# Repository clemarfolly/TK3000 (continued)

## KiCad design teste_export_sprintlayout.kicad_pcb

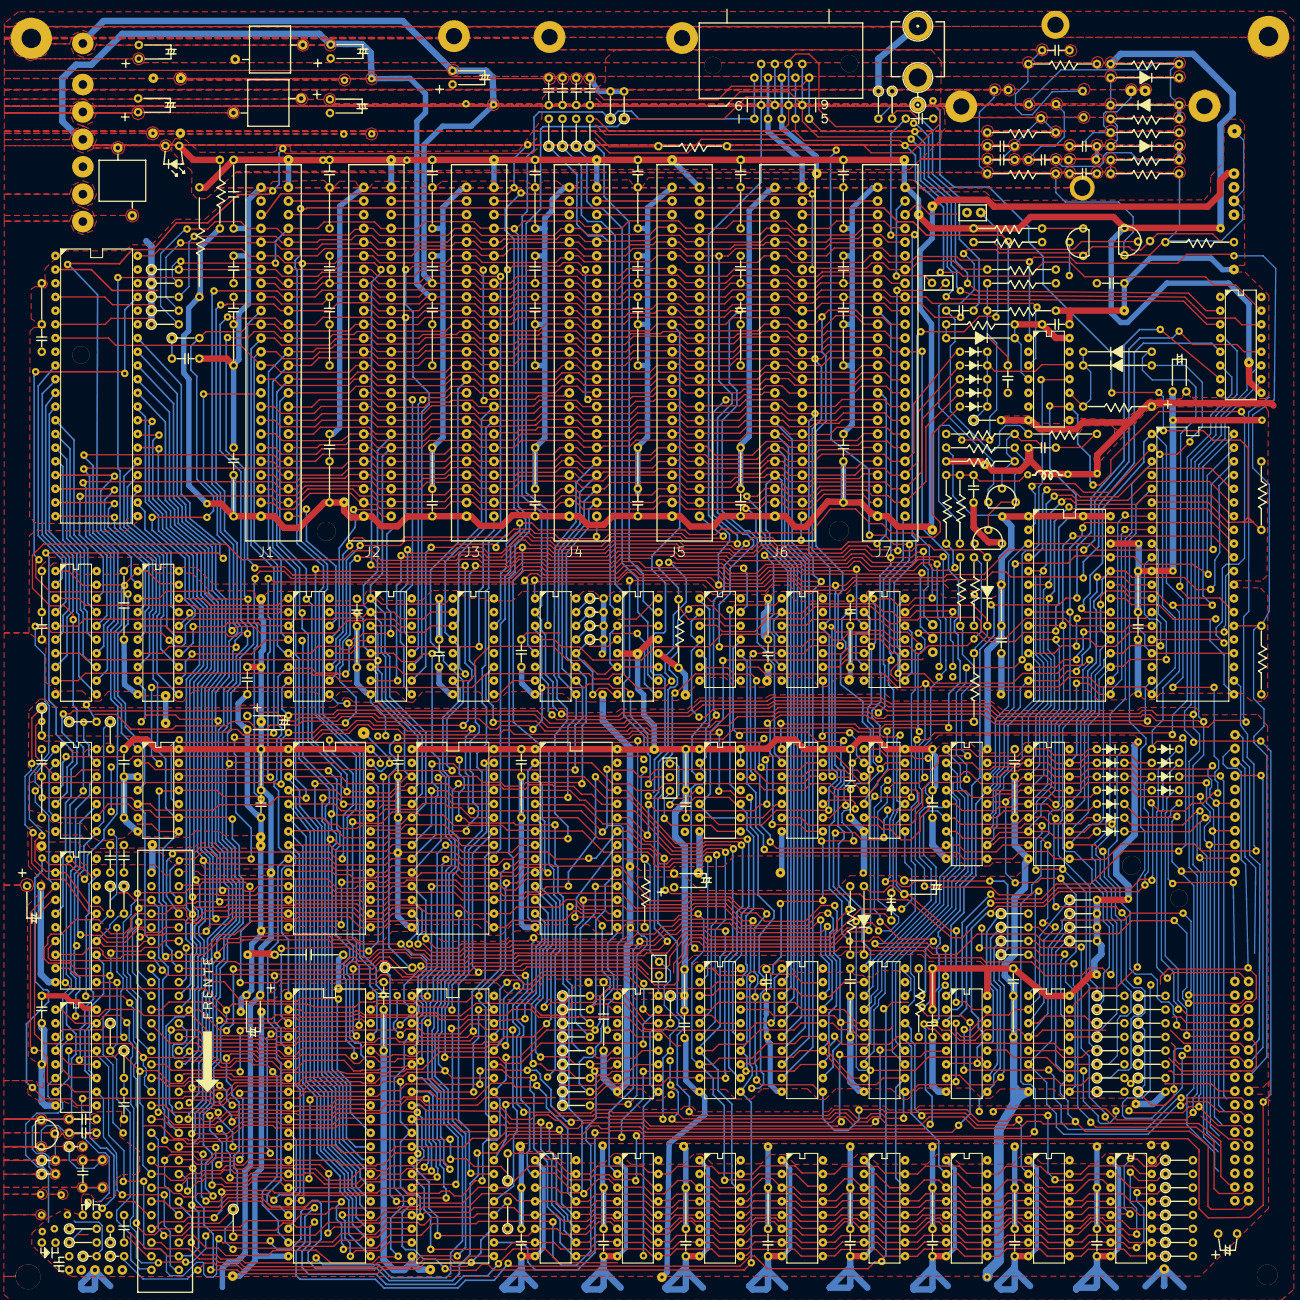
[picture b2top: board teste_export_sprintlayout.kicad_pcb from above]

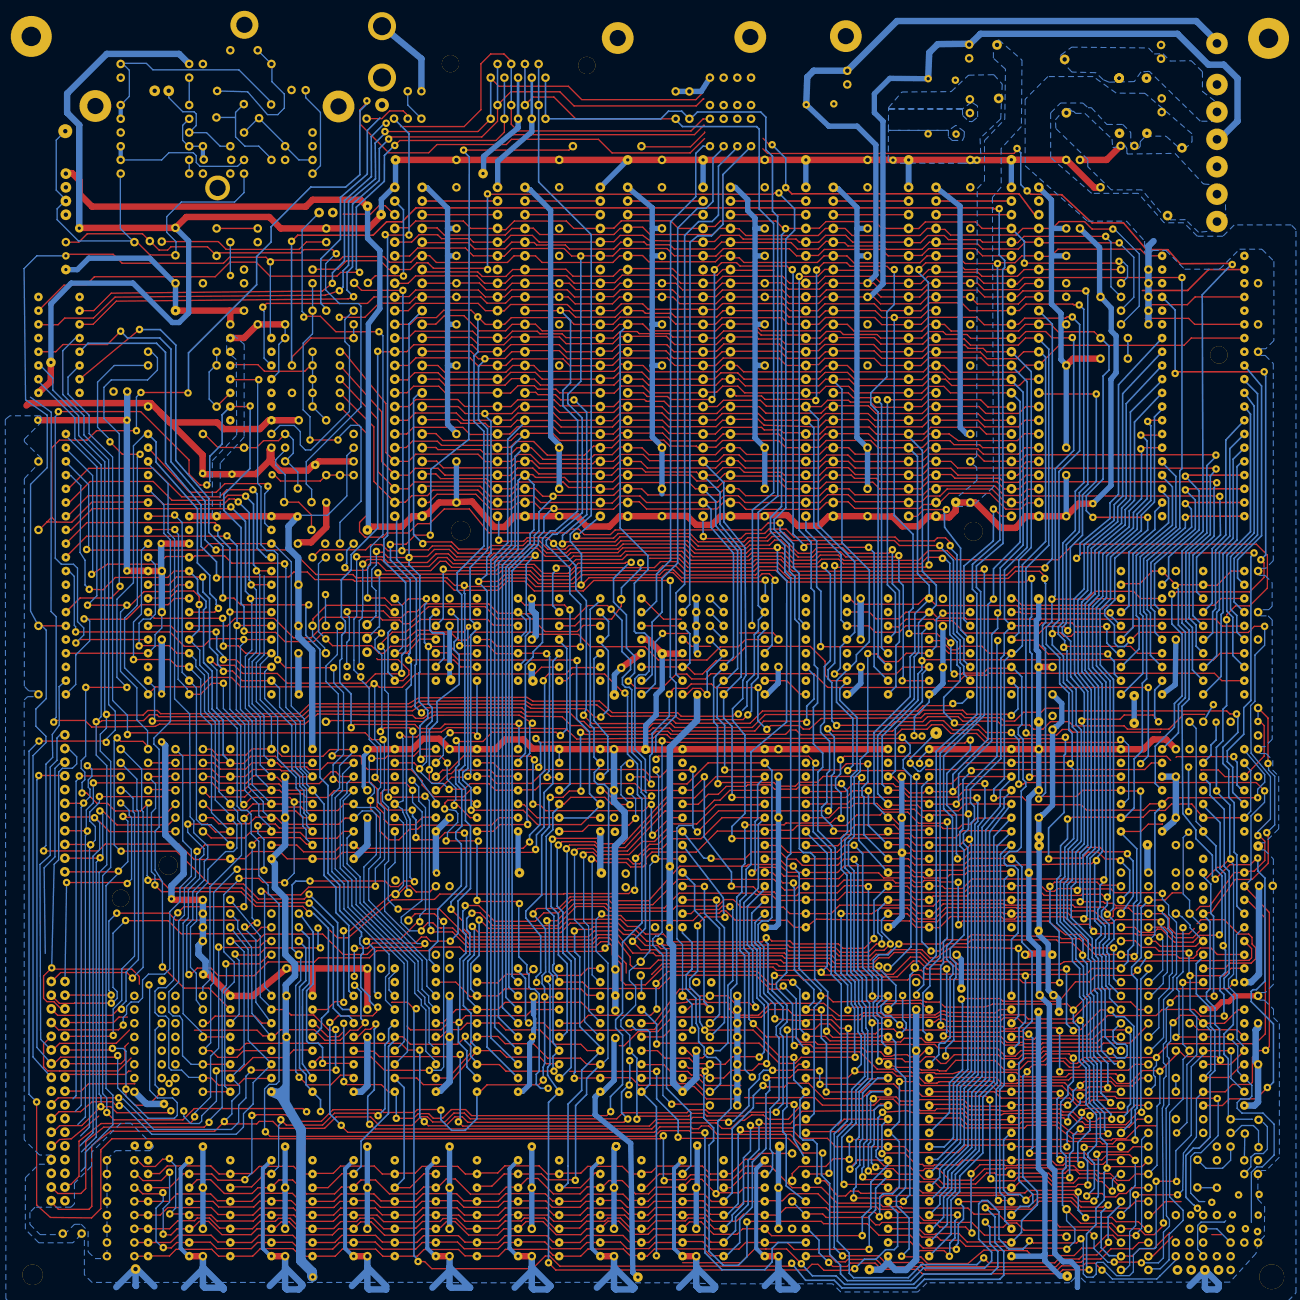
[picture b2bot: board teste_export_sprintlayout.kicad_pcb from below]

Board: 4 copper layers, 1275 parts (962 on the bottom side), 297 nets.

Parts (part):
C: FP_11779_4812_909
C110: 16uF/25V; FP_22677_22885_1261
C#2: FP_11779_5955_910
C#3: FP_11779_3415_911
C#4: FP_11779_8749_912
C#5: FP_13684_4812_913
C#6: FP_13684_5955_914
C#7: FP_13684_3415_915
C#8: FP_13684_8749_916
C#9: FP_730_5701_1057
C#10: FP_4540_12432_1058
C#11: FP_4286_4812_1059
C#12: FP_3397_6463_1060
C#13: FP_6064_4812_1061
C#14: FP_6064_5955_1062
C#15: FP_6064_8495_1063
C#16: FP_6064_3415_1064
C#17: FP_7969_3415_1065
C#18: FP_7969_4812_1066
C#19: FP_7969_5955_1067
C#20: FP_9874_4812_1068
C#21: FP_9874_5955_1069
C#22: FP_9874_3415_1070
C#23: FP_4286_8749_1071
C#24: FP_4286_5955_1072
C#25: FP_7969_8749_1073
C#26: FP_9874_8749_1074
C#27: FP_4286_3415_1075
C#28: FP_2254_11035_1078
C#29: FP_730_11035_1079
C#30: FP_730_14337_1080
C#31: FP_2254_14337_1081
C#32: FP_4794_14337_1082
C#33: FP_15589_4812_1083
C#34: FP_15589_5955_1084
C#35: FP_15589_3415_1085
C#36: FP_15589_8495_1086
C#37: FP_10128_1510_1087
C#38: FP_10382_1510_1088
C#39: FP_10636_1510_1089
C#40: FP_10890_1510_1090
C#41: FP_7334_14337_1097
C#42: FP_9620_14337_1098
C#43: FP_11144_18655_1108
C#44: FP_7067_18655_1111
C#45: FP_9620_22465_1112
C#46: FP_6572_11549_1117
C#47: FP_8096_11543_1118
C#48: FP_9620_11924_1119
C#49: FP_12668_14337_1120
C#50: FP_14192_11543_1121
C#51: FP_15716_11543_1122
C#52: FP_4906_13127_1129
C#53: FP_532_16425_1130
C#54: FP_730_18909_1131
C#55: FP_4758_18543_1132
C#56: FP_5683_17512_1133
C#57: FP_1493_21576_1137
C#58: FP_1493_20814_1138
C#59: FP_1493_20560_1139
C#60: FP_2254_20306_1140
C#61: FP_2255_22592_1141
C#62: FP_1123_23227_1147
C#63: FP_14160_18032_1156
C#64: FP_12642_18420_1158
C#65: FP_15716_14337_1159
C#66: FP_17000_2015_1163
C#67: FP_18516_11289_1167
C#68: FP_18002_8876_1170
C#69: FP_19272_8114_1176
C#70: FP_20542_5066_1177
C#71: FP_19272_2780_1192
C#72: FP_20034_2526_1193
C#73: FP_20034_3034_1194
C#74: FP_19526_748_1195
C#75: FP_18510_2780_1196
C#76: FP_18510_2526_1197
C#77: FP_17748_5574_1200
C#78: FP_18637_6844_1201
C#79: FP_12668_22465_1203
C#80: FP_11144_22465_1204
C#81: FP_14192_22465_1205
C#82: FP_17240_18401_1207
C#83: FP_15716_22465_1208
C#84: FP_17240_22465_1209
C#85: FP_18764_22465_1210
C#86: FP_20288_22465_1211
C#87: FP_18764_14337_1216
C#88: FP_17240_14337_1217
C#89: FP_21050_11035_1225
C#90: FP_19526_5828_1242
C#91: FP_2000_15734_1243
C#92: FP_2254_15734_1244
C#93: FP_15716_18400_1254
C#94: FP_18738_18401_1256
C#95: FP_21765_6883_1257
C#96: FP_16908_16315_1258
C#97: FP_12641_16188_1260
C#98: FP_2718_829_1267
C#99: FP_2706_1820_1268
C#100: FP_6274_823_1269
C#101: FP_8534_1306_1270
C#102: FP_6262_1730_1274
CMP1: Pad_1456_6394_1
CMP2: Pad_1508_8509_2
CMP3: Pad_1512_8252_3
CMP4: Pad_1496_8764_4
CMP5: Pad_1440_9016_5
CMP6: Pad_2078_8643_6
CMP7: Pad_2078_8897_7
CMP8: Pad_2078_9151_8
CMP9: Pad_2078_9405_9
CMP10: Pad_2776_9405_10
CMP11: Pad_2903_8134_11
CMP12: Pad_2903_7881_12
CMP13: Pad_2776_7627_13
CMP14: Pad_3729_7119_14
CMP15: Pad_3792_9151_15
CMP16: Pad_3792_9405_16
CMP17: Pad_4173_6072_17
CMP18: Pad_4173_5691_18
CMP19: Pad_4046_5468_19
CMP20: Pad_3922_5208_20
CMP21: Pad_617_6706_21
CMP22: Pad_2268_6738_22
CMP23: Pad_2141_4960_23
CMP24: Pad_1208_4719_24
CMP25: Pad_805_10064_25
CMP26: Pad_678_10191_26
CMP27: Pad_2329_10826_27
CMP28: Pad_2265_10667_28
CMP29: Pad_1313_11302_29
CMP30: Pad_3091_11683_30
CMP31: Pad_3535_11429_31
CMP32: Pad_3515_11937_32
CMP33: Pad_3472_11175_33
CMP34: Pad_2765_12559_34
CMP35: Pad_2575_13194_35
CMP36: Pad_3026_13219_36
CMP37: Pad_3026_12712_37
CMP38: Pad_1559_12877_38
CMP39: Pad_1508_13201_39
CMP40: Pad_732_13188_40
CMP41: Pad_1129_13049_41
CMP42: Pad_2018_14033_42
CMP43: Pad_2018_14859_43
CMP44: Pad_2018_15240_44
CMP45: Pad_2907_13969_45
CMP46: Pad_2907_14478_46
CMP47: Pad_4000_13178_47
CMP48: Pad_4301_13481_48
CMP49: Pad_4208_13969_49
CMP50: Pad_4263_14997_50
CMP51: Pad_4612_15736_51
CMP52: Pad_4588_16244_52
CMP53: Pad_4079_16319_53
CMP54: Pad_4027_16530_54
CMP55: Pad_3725_15766_55
CMP56: Pad_3960_16846_56
CMP57: Pad_3589_16125_57
CMP58: Pad_3525_16443_58
CMP59: Pad_3525_16760_59
CMP60: Pad_3779_17078_60
CMP61: Pad_3983_17522_61
CMP62: Pad_4281_17776_62
CMP63: Pad_4408_18030_63
CMP64: Pad_3307_4659_64
CMP65: Pad_3303_4317_65
CMP66: Pad_3554_4197_66
CMP67: Pad_3422_4061_67
CMP68: Pad_4257_11504_68
CMP69: Pad_4544_11561_69
CMP70: Pad_4333_11813_70
CMP71: Pad_4094_10164_71
CMP72: Pad_4678_10343_72
CMP73: Pad_4684_10539_73
CMP74: Pad_4928_10539_74
CMP75: Pad_4552_10922_75
CMP76: Pad_4796_10917_76
CMP77: Pad_5062_4693_77
CMP78: Pad_5561_4701_78
CMP79: Pad_5635_9252_79
CMP80: Pad_5804_10363_80
CMP81: Pad_6509_9261_81
CMP82: Pad_6437_9930_82
CMP83: Pad_6630_9928_83
CMP84: Pad_6579_10166_84
CMP85: Pad_6828_10287_85
CMP86: Pad_7509_10005_86
CMP87: Pad_7389_10113_87
CMP88: Pad_7200_11559_88
CMP89: Pad_5011_3354_89
CMP90: Pad_5528_3684_90
CMP91: Pad_5198_2568_91
CMP92: Pad_5303_2777_92
CMP93: Pad_5941_2784_93
CMP94: Pad_7206_2780_94
CMP95: Pad_7497_2784_95
CMP96: Pad_9112_2780_96
CMP97: Pad_7017_4812_97
CMP98: Pad_7473_4812_98
CMP99: Pad_7473_5701_99
CMP100: Pad_7601_7225_100
CMP101: Pad_7791_7225_101
CMP102: Pad_7948_9961_102
CMP103: Pad_8578_10300_103
CMP104: Pad_8768_10300_104
CMP105: Pad_9149_9964_105
CMP106: Pad_9590_9510_106
CMP107: Pad_9639_9962_107
CMP108: Pad_9682_10571_108
CMP109: Pad_9864_10569_109
CMP110: Pad_8928_7240_110
CMP111: Pad_11013_9761_111
CMP112: Pad_11625_10576_112
CMP113: Pad_12174_10247_113
CMP114: Pad_12349_10239_114
CMP115: Pad_12534_10925_115
CMP116: Pad_12721_11107_116
CMP117: Pad_13362_9753_117
CMP118: Pad_13625_9895_118
CMP119: Pad_13788_9890_119
CMP120: Pad_13740_10346_120
CMP121: Pad_14805_9829_121
CMP122: Pad_14128_10109_122
CMP123: Pad_15177_10594_123
CMP124: Pad_15443_10666_124
CMP125: Pad_15833_10366_125
CMP126: Pad_16146_10913_126
CMP127: Pad_16108_11798_127
CMP128: Pad_15530_11784_128
CMP129: Pad_15686_11157_129
CMP130: Pad_15509_9652_130
CMP131: Pad_16072_9735_131
CMP132: Pad_16213_9892_132
CMP133: Pad_16467_10150_133
CMP134: Pad_16599_10024_134
CMP135: Pad_13781_9241_135
CMP136: Pad_13797_9014_136
CMP137: Pad_15062_7481_137
CMP138: Pad_15062_6466_138
CMP139: Pad_15191_5689_139
CMP140: Pad_15011_4812_140
CMP141: Pad_15013_3410_141
CMP142: Pad_15456_2598_142
CMP143: Pad_13411_7228_143
CMP144: Pad_13284_4561_144
CMP145: Pad_9612_3392_145
CMP146: Pad_9489_4054_146
CMP147: Pad_9363_4814_147
CMP148: Pad_9235_4940_148
CMP149: Pad_8914_4821_149
CMP150: Pad_10807_4815_150
CMP151: Pad_10852_7220_151
CMP152: Pad_6426_11731_152
CMP153: Pad_6362_12308_153
CMP154: Pad_5634_10920_154
CMP155: Pad_5557_11176_155
CMP156: Pad_5555_11689_156
CMP157: Pad_6387_12857_157
CMP158: Pad_6359_13216_158
CMP159: Pad_6063_13533_159
CMP160: Pad_5031_13401_160
CMP161: Pad_5303_13394_161
CMP162: Pad_5303_13077_162
CMP163: Pad_6045_14101_163
CMP164: Pad_5794_14341_164
CMP165: Pad_6387_14488_165
CMP166: Pad_6324_14721_166
CMP167: Pad_5941_14606_167
CMP168: Pad_5631_14610_168
CMP169: Pad_6491_15049_169
CMP170: Pad_6098_14902_170
CMP171: Pad_6080_15372_171
CMP172: Pad_6300_15735_172
CMP173: Pad_6288_16169_173
CMP174: Pad_6280_16957_174
CMP175: Pad_6791_17443_175
CMP176: Pad_6502_17775_176
CMP177: Pad_7756_17720_177
CMP178: Pad_7388_17313_178
CMP179: Pad_7545_17313_179
CMP180: Pad_7705_17313_180
CMP181: Pad_7848_17214_181
CMP182: Pad_6523_19388_182
CMP183: Pad_6564_19017_183
CMP184: Pad_6612_18819_184
CMP185: Pad_6230_18334_185
CMP186: Pad_6230_18139_186
CMP187: Pad_4544_17512_187
CMP188: Pad_5043_17903_188
CMP189: Pad_5170_17395_189
CMP190: Pad_4798_17068_190
CMP191: Pad_4420_18571_191
CMP192: Pad_4801_18571_192
CMP193: Pad_4408_18919_193
CMP194: Pad_4154_18919_194
CMP195: Pad_4154_18538_195
CMP196: Pad_4027_18729_196
CMP197: Pad_4154_19427_197
CMP198: Pad_4408_19681_198
CMP199: Pad_5011_19681_199
CMP200: Pad_4980_18983_200
CMP201: Pad_4027_19935_201
CMP202: Pad_4027_20126_202
CMP203: Pad_4260_20300_203
CMP204: Pad_4397_20080_204
CMP205: Pad_4000_20436_205
CMP206: Pad_3847_20495_206
CMP207: Pad_4024_20739_207
CMP208: Pad_4258_20610_208
CMP209: Pad_4275_21073_209
CMP210: Pad_4401_21310_210
CMP211: Pad_4220_21645_211
CMP212: Pad_4010_21404_212
CMP213: Pad_3954_21084_213
CMP214: Pad_3721_21209_214
CMP215: Pad_3529_21467_215
CMP216: Pad_3509_20829_216
CMP217: Pad_3443_20561_217
CMP218: Pad_3463_20254_218
CMP219: Pad_3515_19979_219
CMP220: Pad_4965_21192_220
CMP221: Pad_3885_21780_221
CMP222: Pad_4063_21909_222
CMP223: Pad_3927_22387_223
CMP224: Pad_3906_21983_224
CMP225: Pad_3774_22077_225
CMP226: Pad_3770_22725_226
CMP227: Pad_3509_22153_227
CMP228: Pad_3432_21892_228
CMP229: Pad_3000_21962_229
CMP230: Pad_2990_22718_230
CMP231: Pad_3007_21324_231
CMP232: Pad_3010_20948_232
CMP233: Pad_2889_20432_233
CMP234: Pad_2620_21711_234
CMP235: Pad_2484_22484_235
CMP236: Pad_2223_21962_236
CMP237: Pad_2240_21714_237
CMP238: Pad_2240_20815_238
CMP239: Pad_3458_18536_239
CMP240: Pad_3469_19300_240
CMP241: Pad_3129_18906_241
CMP242: Pad_5702_20201_242
CMP243: Pad_5683_21665_243
CMP244: Pad_6050_21570_244
CMP245: Pad_6285_22091_245
CMP246: Pad_6301_22334_246
CMP247: Pad_6033_22670_247
CMP248: Pad_5786_22466_248
CMP249: Pad_5786_22202_249
CMP250: Pad_5544_22068_250
CMP251: Pad_5032_22062_251
CMP252: Pad_4968_22815_252
CMP253: Pad_4274_22971_253
CMP254: Pad_4013_22777_254
CMP255: Pad_2892_23223_255
CMP256: Pad_3502_22843_256
CMP257: Pad_3397_23209_257
CMP258: Pad_3624_23359_258
CMP259: Pad_3861_23352_259
CMP260: Pad_4268_23469_260
CMP261: Pad_4797_13194_261
CMP262: Pad_4968_14219_262
CMP263: Pad_5166_14350_263
CMP264: Pad_4797_12179_264
CMP265: Pad_3279_13527_265
CMP266: Pad_1181_13840_266
CMP267: Pad_1499_14475_267
CMP268: Pad_737_14602_268
CMP269: Pad_610_14475_269
CMP270: Pad_546_13966_270
CMP271: Pad_569_15249_271
CMP272: Pad_734_15305_272
CMP273: Pad_736_15719_273
CMP274: Pad_3279_15766_274
CMP275: Pad_3153_15640_275
CMP276: Pad_3407_17386_276
CMP277: Pad_3026_17545_277
CMP278: Pad_2963_17799_278
CMP279: Pad_2550_19672_279
CMP280: Pad_2613_19418_280
CMP281: Pad_2252_19043_281
CMP282: Pad_2306_18772_282
CMP283: Pad_2359_18402_283
CMP284: Pad_2125_18027_284
CMP285: Pad_1991_17900_285
CMP286: Pad_2010_17481_286
CMP287: Pad_2122_17011_287
CMP288: Pad_2503_16376_288
CMP289: Pad_2531_16651_289
CMP290: Pad_2528_16903_290
CMP291: Pad_2552_17182_291
CMP292: Pad_1448_17143_292
CMP293: Pad_1377_17344_293
CMP294: Pad_1166_18029_294
CMP295: Pad_1544_18281_295
CMP296: Pad_1357_18649_296
CMP297: Pad_1241_19035_297
CMP298: Pad_1231_19291_298
CMP299: Pad_1427_19466_299
CMP300: Pad_1487_20177_300
CMP301: Pad_558_19973_301
CMP302: Pad_590_19284_302
CMP303: Pad_1523_16112_303
CMP304: Pad_1237_15738_304
CMP305: Pad_4787_15330_305
CMP306: Pad_4788_15491_306
CMP307: Pad_4979_15991_307
CMP308: Pad_2780_15474_308
CMP309: Pad_3306_1265_309
CMP310: Pad_729_15499_310
CMP311: Pad_476_23482_311
CMP312: Pad_6451_23101_312
CMP313: Pad_6321_22973_313
CMP314: Pad_5815_23131_314
CMP315: Pad_7337_23100_315
CMP316: Pad_7305_22084_316
CMP317: Pad_7940_22973_317
CMP318: Pad_8067_22719_318
CMP319: Pad_8226_22021_319
CMP320: Pad_7748_22370_320
CMP321: Pad_7702_21198_321
CMP322: Pad_7819_21449_322
CMP323: Pad_7954_21521_323
CMP324: Pad_8059_21631_324
CMP325: Pad_8406_21769_325
CMP326: Pad_8295_21488_326
CMP327: Pad_8306_21306_327
CMP328: Pad_8300_20932_328
CMP329: Pad_7691_20433_329
CMP330: Pad_7859_20179_330
CMP331: Pad_7379_19864_331
CMP332: Pad_8206_19664_332
CMP333: Pad_8683_21563_333
CMP334: Pad_8800_21187_334
CMP335: Pad_8892_21702_335
CMP336: Pad_7933_23349_336
CMP337: Pad_8689_23216_337
CMP338: Pad_9196_23239_338
CMP339: Pad_9375_23231_339
CMP340: Pad_8432_23094_340
CMP341: Pad_8206_23332_341
CMP342: Pad_8735_20056_342
CMP343: Pad_8850_19914_343
CMP344: Pad_8855_19665_344
CMP345: Pad_8729_18930_345
CMP346: Pad_8198_19413_346
CMP347: Pad_7753_19485_347
CMP348: Pad_7376_18997_348
CMP349: Pad_7373_18812_349
CMP350: Pad_7884_18774_350
CMP351: Pad_8324_18878_351
CMP352: Pad_8334_18537_352
CMP353: Pad_8826_18533_353
CMP354: Pad_8836_18275_354
CMP355: Pad_9598_21064_355
CMP356: Pad_9330_20290_356
CMP357: Pad_9662_20432_357
CMP358: Pad_9981_20617_358
CMP359: Pad_10139_20676_359
CMP360: Pad_10327_20756_360
CMP361: Pad_10544_20617_361
CMP362: Pad_9906_19936_362
CMP363: Pad_9844_19791_363
CMP364: Pad_9729_19654_364
CMP365: Pad_9839_19531_365
CMP366: Pad_9976_19408_366
CMP367: Pad_10105_19780_367
CMP368: Pad_10087_18789_368
CMP369: Pad_10043_18485_369
CMP370: Pad_9688_18700_370
CMP371: Pad_9458_18906_371
CMP372: Pad_9327_19196_372
CMP373: Pad_9335_19416_373
CMP374: Pad_9532_18091_374
CMP375: Pad_9353_18023_375
CMP376: Pad_9695_17897_376
CMP377: Pad_8827_17837_377
CMP378: Pad_7878_18278_378
CMP379: Pad_7318_18268_379
CMP380: Pad_8460_16748_380
CMP381: Pad_7953_16249_381
CMP382: Pad_8217_15741_382
CMP383: Pad_8217_15482_383
CMP384: Pad_8600_15221_384
CMP385: Pad_8458_14984_385
CMP386: Pad_8695_14844_386
CMP387: Pad_7953_14472_387
CMP388: Pad_8076_14229_388
CMP389: Pad_7963_13975_389
CMP390: Pad_8336_14099_390
CMP391: Pad_8470_13899_391
CMP392: Pad_8452_14340_392
CMP393: Pad_8542_13263_393
CMP394: Pad_8708_13324_394
CMP395: Pad_9097_13204_395
CMP396: Pad_8930_13960_396
CMP397: Pad_7059_14213_397
CMP398: Pad_7326_13484_398
CMP399: Pad_7330_15621_399
CMP400: Pad_7327_12434_400
CMP401: Pad_8582_12308_401
CMP402: Pad_7965_11930_402
CMP403: Pad_8840_11801_403
CMP404: Pad_6961_12062_404
CMP405: Pad_609_11425_405
CMP406: Pad_4797_14626_406
CMP407: Pad_1854_22211_407
CMP408: Pad_7062_18260_408
CMP409: Pad_6006_9665_409
CMP410: Pad_9485_3295_410
CMP411: Pad_9737_2499_411
CMP412: Pad_10113_11410_412
CMP413: Pad_10363_13049_413
CMP414: Pad_10188_13066_414
CMP415: Pad_9835_13334_415
CMP416: Pad_9996_12561_416
CMP417: Pad_10944_12690_417
CMP418: Pad_11125_12690_418
CMP419: Pad_9346_15869_419
CMP420: Pad_9343_16182_420
CMP421: Pad_6572_11181_421
CMP422: Pad_10484_14596_422
CMP423: Pad_10617_14087_423
CMP424: Pad_10742_14341_424
CMP425: Pad_10993_14213_425
CMP426: Pad_11206_14072_426
CMP427: Pad_10244_15105_427
CMP428: Pad_10484_15362_428
CMP429: Pad_11122_15237_429
CMP430: Pad_10869_15724_430
CMP431: Pad_10113_15994_431
CMP432: Pad_10493_16240_432
CMP433: Pad_10520_16620_433
CMP434: Pad_11769_11557_434
CMP435: Pad_11774_11932_435
CMP436: Pad_11017_2780_436
CMP437: Pad_12404_12441_437
CMP438: Pad_12466_12661_438
CMP439: Pad_12661_12697_439
CMP440: Pad_12912_13107_440
CMP441: Pad_13233_13072_441
CMP442: Pad_13288_13390_442
CMP443: Pad_13352_12059_443
CMP444: Pad_13288_11805_444
CMP445: Pad_13484_11118_445
CMP446: Pad_13279_10658_446
CMP447: Pad_13918_11932_447
CMP448: Pad_13979_12433_448
CMP449: Pad_14171_12439_449
CMP450: Pad_12084_13708_450
CMP451: Pad_11777_13547_451
CMP452: Pad_11955_15296_452
CMP453: Pad_12268_14986_453
CMP454: Pad_12373_14732_454
CMP455: Pad_11976_14347_455
CMP456: Pad_12651_15233_456
CMP457: Pad_11633_15875_457
CMP458: Pad_12268_15725_458
CMP459: Pad_12286_16316_459
CMP460: Pad_12902_15997_460
CMP461: Pad_13087_15738_461
CMP462: Pad_13240_15662_462
CMP463: Pad_13405_15612_463
CMP464: Pad_13551_15547_464
CMP465: Pad_13699_15479_465
CMP466: Pad_13811_15369_466
CMP467: Pad_10865_18025_467
CMP468: Pad_10611_16818_468
CMP469: Pad_10769_16498_469
CMP470: Pad_10992_16247_470
CMP471: Pad_11119_16977_471
CMP472: Pad_11817_17263_472
CMP473: Pad_12325_17263_473
CMP474: Pad_12897_16755_474
CMP475: Pad_12833_17390_475
CMP476: Pad_13405_17072_476
CMP477: Pad_13913_16882_477
CMP478: Pad_14166_16755_478
CMP479: Pad_14421_16564_479
CMP480: Pad_14103_18025_480
CMP481: Pad_13899_17959_481
CMP482: Pad_13953_18293_482
CMP483: Pad_14249_18777_483
CMP484: Pad_14181_19031_484
CMP485: Pad_13405_19803_485
CMP486: Pad_13781_19670_486
CMP487: Pad_13979_19835_487
CMP488: Pad_13888_19988_488
CMP489: Pad_12244_20561_489
CMP490: Pad_12412_20557_490
CMP491: Pad_12729_20421_491
CMP492: Pad_12380_19294_492
CMP493: Pad_12376_19475_493
CMP494: Pad_11878_19167_494
CMP495: Pad_11873_18520_495
CMP496: Pad_11878_19674_496
CMP497: Pad_12629_21063_497
CMP498: Pad_11739_21700_498
CMP499: Pad_11753_20868_499
CMP500: Pad_11481_20895_500
CMP501: Pad_10983_20812_501
CMP502: Pad_11599_20282_502
CMP503: Pad_10978_19670_503
CMP504: Pad_10987_18909_504
CMP505: Pad_11212_18909_505
CMP506: Pad_11889_18045_506
CMP507: Pad_11118_11936_507
CMP508: Pad_11643_12683_508
CMP509: Pad_13279_14480_509
CMP510: Pad_14122_15561_510
CMP511: Pad_14233_15422_511
CMP512: Pad_14268_15097_512
CMP513: Pad_14171_14721_513
CMP514: Pad_13850_14596_514
CMP515: Pad_13909_14222_515
CMP516: Pad_14063_14038_516
CMP517: Pad_14143_13899_517
CMP518: Pad_14115_13505_518
CMP519: Pad_14181_13219_519
CMP520: Pad_14429_13222_520
CMP521: Pad_13661_13447_521
CMP522: Pad_15197_13462_522
CMP523: Pad_15593_13543_523
CMP524: Pad_15706_13397_524
CMP525: Pad_15756_13959_525
CMP526: Pad_15724_14447_526
CMP527: Pad_15631_14744_527
CMP528: Pad_15808_14810_528
CMP529: Pad_16172_14574_529
CMP530: Pad_16340_15340_530
CMP531: Pad_16408_14831_531
CMP532: Pad_16402_14463_532
CMP533: Pad_16410_14279_533
CMP534: Pad_16271_14063_534
CMP535: Pad_16247_13890_535
CMP536: Pad_16091_14083_536
CMP537: Pad_15316_14834_537
CMP538: Pad_15780_15402_538
CMP539: Pad_15440_15257_539
CMP540: Pad_15182_15405_540
CMP541: Pad_15378_14206_541
CMP542: Pad_16397_13366_542
CMP543: Pad_16236_13029_543
CMP544: Pad_16641_13441_544
CMP545: Pad_9847_17198_545
CMP546: Pad_10206_22464_546
CMP547: Pad_10777_21941_547
CMP548: Pad_13662_5568_548
CMP549: Pad_17249_1685_549
CMP550: Pad_16891_2100_550
CMP551: Pad_16914_2254_551
CMP552: Pad_16845_2393_552
CMP553: Pad_16731_2512_553
CMP554: Pad_16468_4173_554
CMP555: Pad_16909_4165_555
CMP556: Pad_16474_12052_556
CMP557: Pad_16603_12296_557
CMP558: Pad_16990_11798_558
CMP559: Pad_16979_11551_559
CMP560: Pad_17115_12488_560
CMP561: Pad_16997_13376_561
CMP562: Pad_17540_13303_562
CMP563: Pad_17875_14261_563
CMP564: Pad_17892_13826_564
CMP565: Pad_20564_7098_565
CMP566: Pad_21437_7091_566
CMP567: Pad_21520_7798_567
CMP568: Pad_21453_8236_568
CMP569: Pad_22011_8006_569
CMP570: Pad_20216_8805_570
CMP571: Pad_19360_8894_571
CMP572: Pad_19496_9013_572
CMP573: Pad_19633_9118_573
CMP574: Pad_19770_9212_574
CMP575: Pad_20026_9600_575
CMP576: Pad_19842_9747_576
CMP577: Pad_20044_10009_577
CMP578: Pad_19296_10397_578
CMP579: Pad_18774_10267_579
CMP580: Pad_18326_11027_580
CMP581: Pad_19394_10656_581
CMP582: Pad_19407_10909_582
CMP583: Pad_20036_10529_583
CMP584: Pad_20294_10511_584
CMP585: Pad_20357_11023_585
CMP586: Pad_19919_10900_586
CMP587: Pad_20000_11093_587
CMP588: Pad_19788_11159_588
CMP589: Pad_19922_11276_589
CMP590: Pad_20043_11530_590
CMP591: Pad_19909_11792_591
CMP592: Pad_19532_11670_592
CMP593: Pad_19526_11513_593
CMP594: Pad_19656_11410_594
CMP595: Pad_20153_12046_595
CMP596: Pad_19909_12043_596
CMP597: Pad_19909_12260_597
CMP598: Pad_19909_12480_598
CMP599: Pad_20033_9384_599
CMP600: Pad_19083_8828_600
CMP601: Pad_18303_7970_601
CMP602: Pad_17784_7970_602
CMP603: Pad_18534_9389_603
CMP604: Pad_17439_10136_604
CMP605: Pad_17326_10271_605
CMP606: Pad_17656_10339_606
CMP607: Pad_16814_9909_607
CMP608: Pad_17072_10036_608
CMP609: Pad_17045_10434_609
CMP610: Pad_17235_10900_610
CMP611: Pad_20812_9362_611
CMP612: Pad_20808_9631_612
CMP613: Pad_16984_3794_613
CMP614: Pad_17236_3638_614
CMP615: Pad_16718_2780_615
CMP616: Pad_15094_3032_616
CMP617: Pad_6334_9125_617
CMP618: Pad_12414_2780_618
CMP619: Pad_15362_11432_619
CMP620: Pad_16571_4932_620
CMP621: Pad_16581_5198_621
CMP622: Pad_17239_9639_622
CMP623: Pad_17024_5965_623
CMP624: Pad_17048_6327_624
CMP625: Pad_17384_4864_625
CMP626: Pad_17495_5315_626
CMP627: Pad_17757_5204_627
CMP628: Pad_17889_5068_628
CMP629: Pad_17816_4518_629
CMP630: Pad_17760_5697_630
CMP631: Pad_18418_5693_631
CMP632: Pad_18645_4289_632
CMP633: Pad_19038_4669_633
CMP634: Pad_19178_5509_634
CMP635: Pad_19777_4923_635
CMP636: Pad_20796_5574_636
CMP637: Pad_22828_4812_637
CMP638: Pad_22828_4558_638
CMP639: Pad_21812_5955_639
CMP640: Pad_21463_5923_640
CMP641: Pad_11882_23091_641
CMP642: Pad_7005_13966_642
CMP643: Pad_7177_13963_643
CMP644: Pad_6697_13402_644
CMP645: Pad_6959_13460_645
CMP646: Pad_7106_13452_646
CMP647: Pad_11889_13891_647
CMP648: Pad_11889_14084_648
CMP649: Pad_11972_14571_649
CMP650: Pad_11976_14728_650
CMP651: Pad_12629_21063_651
CMP652: Pad_11125_21049_652
CMP653: Pad_12225_23489_653
CMP654: Pad_13386_21693_654
CMP655: Pad_13882_23222_655
CMP656: Pad_14191_21068_656
CMP657: Pad_15552_20609_657
CMP658: Pad_15877_20391_658
CMP659: Pad_16185_20606_659
CMP660: Pad_16704_20544_660
CMP661: Pad_17041_20495_661
CMP662: Pad_17198_20654_662
CMP663: Pad_17724_20674_663
CMP664: Pad_17676_19864_664
CMP665: Pad_18108_20418_665
CMP666: Pad_18366_20422_666
CMP667: Pad_18843_20571_667
CMP668: Pad_19129_20794_668
CMP669: Pad_19380_20491_669
CMP670: Pad_19394_19648_670
CMP671: Pad_17819_19652_671
CMP672: Pad_18070_19526_672
CMP673: Pad_18505_19784_673
CMP674: Pad_17828_18898_674
CMP675: Pad_17936_18767_675
CMP676: Pad_17678_18783_676
CMP677: Pad_17678_18394_677
CMP678: Pad_17083_18796_678
CMP679: Pad_17279_18772_679
CMP680: Pad_17046_18483_680
CMP681: Pad_17043_18268_681
CMP682: Pad_17477_18078_682
CMP683: Pad_17483_17912_683
CMP684: Pad_15716_21068_684
CMP685: Pad_17240_21068_685
CMP686: Pad_18764_21068_686
CMP687: Pad_20288_21068_687
CMP688: Pad_19510_21683_688
CMP689: Pad_19891_20604_689
CMP690: Pad_20174_20619_690
CMP691: Pad_20442_20515_691
CMP692: Pad_20643_20408_692
CMP693: Pad_20882_20405_693
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
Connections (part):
Net-2: CMP2.1, CMP250.1, CMP387.1, CMP422.1, CMP906.15, CMP907.15, CMP1017.36, CMP1034.14, CMP1043.16, D#22.2, J1.44, J2.44, J3.44, J4.44, J5.44, J6.44, J7.44
Net-3: CMP3.1, CMP428.1, CMP906.12, CMP907.12, CMP1017.34, CMP1034.18, D#21.2, J1.42, J2.42, J3.42, J4.42, J5.42, J6.42, J7.42
Net-4: CMP4.1, CMP389.1, CMP423.1, CMP906.17, CMP907.17, CMP1017.37, CMP1034.10, CMP1043.14, D#23.2, J1.46, J2.46, J3.46, J4.46, J5.46, J6.46, J7.46
Net-5: CMP5.1, CMP388.1, CMP424.1, CMP906.19, CMP907.19, CMP1017.38, CMP1034.7, CMP1043.13, D#24.2, J1.48, J2.48, J3.48, J4.48, J5.48, J6.48, J7.48
Net-6: CMP6.1, CMP1033.37, CMP1035.2
Net-7: CMP7.1, CMP1033.38, CMP1035.4
Net-8: CMP8.1, CMP1033.39, CMP1035.11
Net-9: CMP9.1, CMP1033.40, CMP1035.15
Net-10: CMP10.1, CMP16.1, CMP30.1, CMP272.1, CMP405.1, CMP1038.2, J1.21, J2.21, J3.21, J4.21, J5.21, J6.21, J7.21, R#30.2
Net-11: CMP11.1, CMP55.1, CMP199.1, CMP478.1, CMP482.1, CMP487.1, CMP658.1, CMP669.1, CMP688.1, CMP906.20, CMP907.20, CMP1016.2, CMP1016.7, CMP1017.39, CMP1018.31, CMP1020.7, CMP1021.20, CMP1025.30, CMP1033.29, R#49.2
Net-12: CMP12.1, CMP57.1, CMP718.1, CMP755.1, CMP906.21, CMP907.21, CMP1020.8, CMP1021.18, CMP1025.28, CMP1033.28
Net-13: CMP13.1, CMP58.1, CMP477.1, CMP486.1, CMP753.1, CMP906.22, CMP907.22, CMP1014.2, CMP1014.7, CMP1020.14, CMP1021.16, CMP1022.13, CMP1025.22, CMP1033.27
Net-14: CMP14.1, CMP68.1, CMP1041.7, J1.31
Net-15: C#4.3, C#8.3, C#15.1, C#15.2, C#23.1, C#23.2, C#25.3, C#26.3, C#36.1, C#36.2, CMP15.1, CMP614.1, CMP617.1, CMP622.1, CMP949.1, CMP1273.2, J1.49, J2.49, J3.49, J4.49, J5.49, J6.49, J7.49, R#31.1, R#32.1
Net-16: CMP17.1, CMP49.1, CMP75.1, CMP216.1, CMP906.2, CMP1017.20, CMP1035.3, J1.24, J2.24, J3.24, J4.24, J5.24, J6.24, J7.24
Net-17: CMP18.1, CMP61.1, CMP69.1, CMP128.1, CMP139.1, CMP175.1, CMP217.1, CMP447.1, CMP515.1, CMP906.7, CMP1017.18, CMP1035.9, CMP1046.9, CMP1048.7, J1.22, J2.22, J3.22, J4.22, J5.22, J6.22, J7.22
Net-18: CMP19.1, CMP70.1, CMP218.1, CMP228.1, CMP242.1, CMP243.1, CMP342.1, CMP353.1, CMP420.1, CMP908.19, CMP1017.16, CMP1018.6, CMP1025.46, CMP1035.12, J1.20, J2.20, J3.20, J4.20, J5.20, J6.20, J7.20
Net-19: CMP20.1, CMP35.1, CMP47.1, CMP202.1, CMP208.1, CMP219.1, CMP318.1, CMP329.1, CMP634.1, CMP826.1, CMP829.1, CMP1007.3, CMP1009.11, CMP1010.11, CMP1011.11, CMP1012.11, CMP1013.11, CMP1014.11, CMP1015.11, CMP1016.11, CMP1017.14, CMP1017.19, CMP1018.25, CMP1025.34, CMP1035.17, J1.18, J2.18, J3.18, J4.18, J5.18, J6.18, J7.18, R#18.1
Net-20: CMP21.1, CMP22.1, CMP26.1, CMP27.1, CMP1033.8, CMP1037.4
Net-21: CMP23.1, CMP50.1, CMP196.1, CMP215.1, CMP259.1, CMP337.1, CMP1017.7, CMP1018.32, CMP1025.43, CMP1036.2, CMP1036.11, CMP1036.13, CMP1037.13, J1.16, J2.16, J3.16, J4.16, J5.16, J6.16, J7.16
Net-22: C.2, C110.1, C110.2, C#2.1, C#2.2, C#2.3, C#3.2, C#3.3, C#4.1, C#4.2, C#5.2, C#6.3, C#7.2, C#7.3, C#8.1, C#8.2, C#9.1, C#9.2, C#9.3, C#10.1, C#10.2, C#12.1, C#13.2, C#14.3, C#15.3, C#16.2, C#16.3, C#17.2, C#17.3, C#18.2, C#19.3, C#20.2, C#21.3, C#22.2, C#22.3, C#23.3, C#24.1, C#24.2, C#25.1, C#25.2, C#26.1, C#26.2, C#27.2, C#28.1, C#28.2, C#29.1, C#29.2, C#29.3, C#30.1, C#30.2, C#30.3, C#31.1, C#31.2, C#31.3, C#32.1, C#32.2, C#32.3, C#33.1, C#33.2, C#34.1, C#34.3, C#35.1, C#35.2, C#35.3, C#36.3, C#37.1, C#37.2, C#38.1, C#38.2, C#39.1, C#39.2, C#40.1, C#40.2, C#41.1, C#41.2, C#42.1, C#42.2, C#42.3, C#43.1, C#43.2, C#44.3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
Net-23: CMP25.1, CMP71.1, CMP1033.14, CMP1036.9
Net-24: CMP28.1, CMP1034.1, CMP1034.6, CMP1035.1, CMP1035.6, CMP1037.1
Net-25: CMP31.1, CMP171.1, CMP906.16, CMP907.16, CMP1017.27, CMP1035.14, CMP1040.3, J1.28, J2.28, J3.28, J4.28, J5.28, J6.28, J7.28
Net-26: CMP32.1, CMP520.1, CMP562.1, CMP624.1, CMP1035.18, CMP1040.4, CMP1049.1, J1.26, J2.26, J3.26, J4.26, J5.26, J6.26, J7.26
Net-27: CMP33.1, CMP1035.10, CMP1040.2
Net-28: CMP34.1, CMP45.1, CMP114.1, CMP437.1, CMP606.1, R#79.1
Net-29: CMP39.1, CMP1036.6
Net-30: CMP41.1, CMP415.1, CMP416.1, CMP455.1, CMP508.1, CMP1038.9, CMP1262.2
Net-31: CMP42.1, CMP43.1
Net-32: CMP44.1, CMP1025.9, CMP1038.13, R#55.2
Net-33: CMP46.1, CMP73.1, CMP125.1, CMP178.1, CMP277.1, CMP406.1, CMP1018.9, CMP1025.14, CMP1037.8, CMP1047.3
Net-34: CMP48.1, CMP51.1, CMP274.1, CMP386.1, CMP394.1, CMP426.1, CMP429.1, CMP505.1, CMP1019.1, CMP1019.8, CMP1025.6, CMP1049.7
Net-35: CMP52.1, CMP63.1, CMP357.1, CMP365.1, CMP376.1, CMP489.1, CMP492.1, CMP641.1, CMP648.1, CMP908.18, CMP908.25, CMP908.28, CMP917.1, CMP1019.13, CMP1019.14, CMP1019.16, CMP1025.4, R#45.2, R#46.2, R#72.2, R#73.2
Net-36: CMP53.1, CMP181.1, CMP288.1, CMP545.1, CMP720.1, CMP906.23, CMP907.23, CMP1009.2, CMP1009.7, CMP1020.3, CMP1021.7, CMP1022.2, CMP1025.27, CMP1033.16
Net-37: CMP54.1, CMP180.1, CMP289.1, CMP472.1, CMP721.1, CMP906.24, CMP907.24, CMP1010.2, CMP1010.7, CMP1020.4, CMP1021.8, CMP1022.9, CMP1025.25, CMP1033.18
Net-38: CMP56.1, CMP179.1, CMP290.1, CMP476.1, CMP906.25, CMP907.25, CMP1011.2, CMP1011.7, CMP1020.12, CMP1021.10, CMP1022.11, CMP1025.19, CMP1033.20
Net-39: CMP59.1, CMP719.1, CMP906.27, CMP907.27, CMP1013.2, CMP1013.7, CMP1020.16, CMP1021.14, CMP1022.18, CMP1025.20, CMP1033.22
Net-40: CMP60.1, CMP291.1, CMP474.1, CMP654.1, CMP906.28, CMP907.28, CMP1012.2, CMP1012.7, CMP1020.15, CMP1021.13, CMP1022.17, CMP1025.17, CMP1033.21
Net-41: CMP62.1, CMP194.1, CMP239.1, CMP1025.40
Net-42: CMP64.1, CMP77.1, CMP146.1, CMP372.1, CMP1017.10, J1.8, J2.8, J3.8, J4.8, J5.8, J6.8, J7.8, R#26.2
Net-43: CMP65.1, J1.9, J2.9, J3.9, J4.9, J5.9, J6.9, J7.9, R#28.2
Net-44: CMP66.1, J1.10, J2.10, J3.10, J4.10, J5.10, J6.10, J7.10, R#27.2
Net-45: CMP67.1, J1.7, J2.7, J3.7, J4.7, J5.7, J6.7, J7.7, R#29.2
Net-46: CMP72.1, J1.19
Net-47: CMP74.1, CMP262.1, CMP609.1, CMP999.1, CMP1037.7
Net-48: CMP78.1, CMP408.1, CMP633.1, CMP638.1, CMP968.1, CMP1005.29, CMP1007.1, CMP1033.5, J1.11, J2.11, J3.11, J4.11, J5.11, J6.11, J7.11, R#109.2
Net-49: CMP79.1, CMP1040.7, J1.50
Net-50: CMP80.1, CMP120.1, CMP1017.13, CMP1045.6
Net-51: CMP81.1, CMP1040.8, J2.50
Net-52: CMP82.1, CMP111.1, CMP1040.13, J4.50
Net-53: CMP83.1, CMP117.1, CMP1040.14, J5.50
Net-54: CMP84.1, CMP133.1, CMP158.1, CMP161.1, CMP229.1, CMP236.1, CMP263.1, CMP269.1, CMP302.1, CMP525.1, CMP527.1, CMP535.1, CMP608.1, CMP998.1, CMP1025.60, CMP1038.3, CMP1039.14, CMP1049.13, J7.19
Net-55: CMP85.1, CMP97.1, CMP103.1, CMP393.1, J1.14
Net-56: CMP86.1, CMP118.1, CMP143.1, CMP1041.16, J6.31
Net-57: CMP87.1, CMP132.1, CMP400.1, CMP1041.12, J7.31
Net-58: CMP88.1, CMP99.1, CMP152.1, CMP153.1, CMP548.1, CMP1017.1, CMP1040.11, CMP1049.2, J2.19, J3.19, J4.19, J5.19, J6.19
Net-59: C#78.1, CMP90.1, CMP632.1, CMP1017.8, D#20.2, R#86.1
Net-60: CMP98.1, CMP110.1, CMP149.1, CMP1041.13, J4.31
Net-61: CMP100.1, CMP1041.8, J2.31
Net-62: CMP101.1, CMP1041.10, J3.31
Net-63: CMP102.1, CMP105.1, CMP147.1, CMP150.1, CMP151.1, CMP1041.14, J5.31
Net-64: CMP104.1, CMP384.1, CMP605.1, CMP906.14, CMP947.1
Net-65: CMP106.1, CMP1042.7, D#25.2
Net-66: CMP108.1, CMP123.1, CMP137.1, CMP1021.17, CMP1043.9, J1.33, J2.33, J3.33, J4.33, J5.33, J6.33, J7.33
Net-67: CMP113.1, CMP115.1, CMP1045.7, R#71.2
Net-68: CMP116.1, CMP189.1, CMP473.1, CMP836.1, CMP837.1, CMP1017.3, CMP1046.2, CMP1046.4
Net-69: CMP119.1, CMP121.1, CMP157.1, CMP441.1, CMP1040.16, J6.50
Net-70: CMP122.1, CMP532.1, CMP604.1, CMP728.1, CMP757.1, CMP948.1, CMP1046.11
Net-71: CMP126.1, CMP127.1, CMP340.1, CMP351.1, CMP370.1, CMP526.1, CMP534.1, CMP610.1, CMP623.1, CMP631.1, CMP908.2, CMP1018.7, CMP1025.55, CMP1046.10, CMP1049.4, CMP1050.6, CMP1259.2
Net-72: CMP129.1, CMP536.1, CMP1049.3
Net-74: CMP135.1, CMP1021.2, J1.47, J2.47, J3.47, J4.47, J5.47, J6.47, J7.47
Net-75: CMP136.1, CMP1021.3, J1.45, J2.45, J3.45, J4.45, J5.45, J6.45, J7.45
Net-76: CMP138.1, CMP168.1, CMP268.1, CMP541.1, CMP1025.11, CMP1036.1, CMP1037.9, CMP1038.14, CMP1040.9, CMP1041.4, CMP1046.7, CMP1050.4, J1.25, J2.25, J3.25, J4.25, J5.25, J6.25, J7.25, R#56.2
Net-77: CMP144.1, CMP444.1, CMP1046.8, J1.12, J2.12, J3.12, J4.12, J5.12, J6.12, J7.12
Net-78: CMP148.1, CMP352.1, CMP1017.6, J1.13, J2.13, J3.13, R#25.2
Net-79: CMP154.1, CMP164.1, CMP165.1, CMP906.8, CMP907.8, CMP1017.29, J1.32, J2.32, J3.32, J4.32, J5.32, J6.32, J7.32
Net-80: CMP155.1, CMP166.1, CMP167.1, CMP906.10, CMP907.10, CMP1017.28, J1.30, J2.30, J3.30, J4.30, J5.30, J6.30, J7.30
Net-81: CMP156.1, CMP170.1, CMP906.13, CMP907.13, CMP1017.22
Net-82: CMP159.1, CMP172.1, CMP275.1, CMP451.1, CMP502.1, CMP516.1, CMP518.1, CMP1025.8, CMP1049.6, R#47.2
Net-83: CMP160.1, J1.23, J2.23, J3.23, J4.23, J5.23, J6.23, J7.23
Net-84: CMP162.1, CMP543.1, CMP1040.12, J7.50
Net-85: CMP163.1, CMP182.1, CMP1037.2
Net-86: CMP169.1, CMP184.1, CMP193.1, CMP198.1, CMP461.1, CMP908.12, CMP1020.2, CMP1025.29
Net-87: CMP173.1, CMP174.1, CMP276.1, CMP431.1, CMP465.1, CMP908.3, CMP1020.18, CMP1025.18
Net-88: CMP176.1, CMP183.1, CMP241.1, CMP377.1, CMP529.1, CMP558.1, CMP727.1, CMP756.1, CMP907.14, CMP1025.38, CMP1046.3
Net-89: CMP177.1, CMP730.1, CMP1018.2, CMP1050.14
Net-90: CMP185.1, CMP278.1, CMP1017.21, CMP1025.13, CMP1038.15
Net-91: CMP188.1, CMP316.1, CMP341.1, CMP390.1, CMP397.1, CMP481.1, CMP655.1, CMP1017.9, CMP1018.36, CMP1020.1, CMP1020.20, CMP1025.16, CMP1037.14, CMP1042.11, J1.29, J2.29, J3.29, J4.29, J5.29, J6.29, J7.29, R#57.1
Net-92: CMP195.1, CMP224.1, CMP294.1, CMP354.1, CMP419.1, CMP908.17, CMP1018.20, CMP1025.47, CMP1038.11
Net-93: CMP197.1, CMP235.1, CMP253.1, CMP283.1, CMP295.1, CMP1017.11, CMP1018.38, CMP1025.54, CMP1038.6, R#58.1
Net-94: CMP200.1, CMP220.1, CMP231.1, CMP349.1, CMP378.1, CMP383.1, CMP908.15, CMP1018.1, CMP1025.52
Net-95: CMP201.1, CMP203.1, CMP317.1, CMP323.1, CMP330.1, CMP825.1, CMP828.1, CMP1009.12, CMP1010.12, CMP1011.12, CMP1012.12, CMP1013.12, CMP1014.12, CMP1015.12, CMP1016.12, CMP1017.17, CMP1018.26, CMP1025.31, R#19.1
Net-96: CMP204.1, CMP210.1, CMP320.1, CMP331.1, CMP827.1, CMP830.1, CMP1009.9, CMP1010.9, CMP1011.9, CMP1012.9, CMP1013.9, CMP1014.9, CMP1015.9, CMP1016.9, CMP1017.15, CMP1018.23, CMP1025.44, R#17.1
Net-97: CMP205.1, CMP209.1, CMP360.1, CMP1009.10, CMP1010.10, CMP1011.10, CMP1012.10, CMP1013.10, CMP1014.10, CMP1015.10, CMP1016.10, CMP1017.24, CMP1018.24, CMP1025.36, R#21.1
Net-98: CMP206.1, CMP212.1, CMP321.1, CMP359.1, CMP1009.13, CMP1010.13, CMP1011.13, CMP1012.13, CMP1013.13, CMP1014.13, CMP1015.13, CMP1016.13, CMP1017.25, CMP1018.19, CMP1025.35, R#22.1
Net-99: CMP207.1, CMP211.1, CMP322.1, CMP358.1, CMP1009.14, CMP1010.14, CMP1011.14, CMP1012.14, CMP1013.14, CMP1014.14, CMP1015.14, CMP1016.14, CMP1017.26, CMP1018.17, CMP1025.37, R#23.1
Net-100: CMP213.1, CMP221.1, CMP324.1, CMP362.1, CMP1009.8, CMP1010.8, CMP1011.8, CMP1012.8, CMP1013.8, CMP1014.8, CMP1015.8, CMP1016.8, CMP1017.35, CMP1018.15, CMP1025.42, R#20.1
Net-101: CMP214.1, CMP225.1, CMP251.1, CMP1017.23, CMP1018.21, CMP1025.41
Net-102: CMP222.1, CMP223.1, CMP335.1, CMP373.1, CMP468.1, CMP471.1, CMP504.1, CMP908.16, CMP1018.16, CMP1025.53
Net-103: CMP226.1, CMP248.1, CMP255.1, CMP257.1, CMP282.1, CMP338.1, CMP1039.1, CMP1039.6, CMP1039.9, CMP1039.13
Net-104: CMP227.1, CMP245.1, CMP313.1, CMP503.1, CMP546.1, CMP1019.11, CMP1025.58
Net-105: CMP230.1, CMP232.1, CMP327.1, CMP328.1, CMP498.1, CMP499.1, CMP769.1, CMP849.1, CMP850.1, CMP1008.4, CMP1018.29, CMP1025.5, CMP1025.39, R#48.1
Net-106: CMP233.1, CMP1025.15
Net-107: CMP234.1, CMP237.1, CMP252.1, CMP254.1, CMP298.1, CMP334.1, CMP496.1, CMP500.1, CMP1039.8, CMP1039.12
Net-108: CMP240.1, CMP347.1, CMP381.1, CMP425.1, CMP432.1, CMP466.1, CMP908.8, CMP1020.13, CMP1025.24
Net-109: CMP246.1, CMP312.1, CMP404.1, CMP906.4, CMP907.4, CMP1017.31, CMP1018.39, CMP1034.12, CMP1041.3, CMP1042.3, J1.36, J2.36, J3.36, J4.36, J5.36, J6.36, J7.36
Net-110: CMP249.1, CMP339.1, CMP713.1, CMP752.1, CMP1025.49
Net-111: CMP256.1, CMP314.1, CMP1025.50, CMP1042.12, CMP1044.3, CMP1044.7, CMP1044.11, CMP1044.13
Net-112: CMP258.1, CMP1018.34, R#64.2
Net-113: CMP265.1, CMP442.1, CMP480.1, CMP509.1, CMP514.1, CMP1037.10
Net-114: CMP266.1, CMP1036.4
Net-115: CMP280.1, CMP374.1, CMP438.1, CMP454.1, CMP491.1, CMP660.1, CMP664.1, CMP676.1, CMP1018.10, CMP1018.11, CMP1020.6, CMP1022.20, CMP1023.7, CMP1025.32, CMP1025.33, CMP1038.4, CMP1045.14, CMP1048.10, CMP1262.1
Net-116: CMP281.1, CMP287.1, CMP297.1, CMP1039.7, CMP1039.11
Net-117: CMP284.1, CMP1025.59, CMP1038.20, R#53.2
Net-118: CMP292.1, CMP1025.10, CMP1036.14, R#51.1
Net-119: CMP293.1, CMP296.1, CMP1017.4, CMP1036.10
Net-120: CMP300.1, CMP332.1, CMP392.1, CMP908.10, CMP1018.14
Net-121: CMP319.1, CMP343.1, CMP344.1, CMP363.1, CMP1009.16, CMP1010.16, CMP1011.16, CMP1012.16, CMP1013.16, CMP1014.16, CMP1015.16, CMP1016.16, CMP1018.12, R#24.1
Net-122: CMP325.1, CMP402.1, CMP421.1, CMP1018.35, CMP1040.6, CMP1041.9
Net-123: CMP326.1, CMP350.1, CMP382.1, CMP430.1, CMP458.1, CMP459.1, CMP908.14, CMP1018.3, CMP1025.48
Net-124: CMP333.1, CMP396.1, CMP647.1, CMP1018.28
Net-125: C#44.1, C#44.2, CMP336.1, CMP1018.40
Net-126: CMP346.1, CMP380.1, CMP494.1, CMP1019.6, CMP1025.7
Net-127: CMP348.1, CMP371.1, CMP379.1, CMP1018.30
Net-128: CMP356.1, CMP1018.27
Net-129: CMP361.1, CMP364.1, CMP657.1, CMP754.1, CMP1018.13, CMP1023.9
Net-130: CMP366.1, CMP908.24, CMP1019.10, R#44.2
Net-131: CMP368.1, CMP462.1, CMP908.11, CMP1020.9, CMP1025.23
Net-132: CMP369.1, CMP908.23, CMP1019.7, R#39.2
Net-133: CMP385.1, CMP391.1, CMP427.1, CMP547.1, CMP1009.3, CMP1010.3, CMP1011.3, CMP1012.3, CMP1013.3, CMP1014.3, CMP1015.3, CMP1016.3
Net-134: CMP395.1, CMP852.1, CMP1042.13
Net-135: CMP398.1, CMP544.1, CMP1050.10, D#26.1, R#57.2
Net-136: CMP401.1, CMP906.3, CMP907.3, CMP1017.30, CMP1041.11, CMP1042.4, J1.34, J2.34, J3.34, J4.34, J5.34, J6.34, J7.34
Net-137: CMP403.1, CMP1040.10, J3.50
Net-138: CMP407.1, CMP1038.16
Net-140: CMP413.1, CMP666.1, CMP767.1, CMP823.1, CMP1008.13
Net-141: CMP414.1, CMP693.1, CMP768.1, CMP822.1, CMP976.1, CMP1008.14, CMP1043.3
Net-142: CMP417.1, CMP1043.10, CMP1044.15, R#70.1
Net-143: CMP433.1, CMP908.27, CMP1019.9, R#43.2
Net-144: CMP434.1, CMP1044.16
Net-145: CMP440.1, CMP772.1, CMP1005.39, CMP1045.2, CMP1045.4
Net-146: CMP443.1, CMP1047.9, CMP1048.9, CMP1048.13, CMP1049.9
Net-147: CMP445.1, CMP1046.1, CMP1048.8
Net-148: CMP448.1, CMP511.1, CMP904.15, CMP905.15, CMP1045.11
Net-149: CMP452.1, CMP513.1, CMP517.1, CMP650.1, CMP908.13, CMP1050.3
Net-150: CMP453.1, CMP1048.14, CMP1262.3
Net-152: CMP463.1, CMP908.9, CMP1020.11
Net-153: CMP464.1, CMP485.1, CMP908.4, CMP1020.17
Net-154: CMP469.1, CMP908.22, R#42.2
Net-155: CMP470.1, CMP908.21, R#41.2
Net-156: CMP475.1, CMP708.1, CMP1005.3, CMP1045.1, CMP1048.2
Net-157: CMP479.1, CMP488.1, CMP528.1, CMP538.1, CMP540.1, CMP717.1, CMP1049.10
Net-158: CMP483.1, CMP1017.2, CMP1021.1
Net-159: CMP490.1, CMP493.1, CMP659.1, CMP715.1, CMP751.1, CMP1024.10
Net-160: C#66.2, CMP501.1, CMP554.1, CMP555.1, CMP557.1, CMP595.1, CMP668.1, CMP1018.33
Net-161: CMP510.1, CMP847.1, CMP904.18, CMP905.18, CMP1005.33, CMP1045.10
Net-162: CMP512.1, CMP519.1, CMP1049.14, R#76.1
Net-163: CMP522.1, CMP524.1, CMP1046.14, CMP1050.2
Net-164: CMP530.1, CMP531.1, CMP539.1, CMP722.1, CMP1038.12, CMP1050.8
Net-165: CMP533.1, CMP681.1, CMP729.1, CMP733.1
Net-166: CMP537.1, CMP619.1, CMP1047.8, CMP1048.11
Net-167: CMP542.1, CMP559.1, CMP561.1, CMP570.1, CMP593.1, CMP776.1, CMP816.1, CMP820.1, CMP1005.36, CMP1007.13, CMP1050.9
Net-168: CMP550.1, CMP628.1, CMP1008.2
Net-169: CMP560.1, CMP568.1, CMP569.1, CMP731.1, CMP746.1, CMP1005.40, CMP1024.1, CMP1045.13, D#15.2
Net-170: CMP563.1, CMP819.1, CMP840.1, CMP845.1, CMP1007.8, CMP1050.11
Net-171: CMP564.1, CMP1049.8, R#78.1
Net-172: CMP571.1, CMP1005.10, CMP1006.4
Net-173: CMP572.1, CMP578.1, CMP904.2, CMP905.2, CMP1005.13, CMP1006.9, CMP1022.14, D#12.2
Net-174: CMP573.1, CMP581.1, CMP904.3, CMP905.3, CMP1005.14, CMP1006.11, CMP1022.16, D#11.2
Net-175: CMP574.1, CMP582.1, CMP904.4, CMP905.4, CMP1005.16, CMP1006.12, CMP1022.15, D#8.2
Net-176: CMP575.1, CMP588.1, CMP904.12, CMP905.12, CMP1005.18, CMP1006.15, CMP1022.12, D#10.2
Net-177: CMP576.1, CMP594.1, CMP904.11, CMP905.11, CMP1005.20, CMP1006.17, CMP1022.4, D#9.2
Net-178: CMP579.1, CMP812.1, CMP904.8, CMP905.8, CMP1005.6, CMP1006.8, CMP1023.1, D.2
Net-179: CMP580.1, CMP586.1, CMP640.1, CMP663.1, CMP675.1, CMP680.1, CMP1008.12, CMP1018.22
Net-180: CMP584.1, CMP597.1, CMP743.1, CMP766.1, CMP799.1, CMP904.13, CMP1005.24, CMP1006.25, CMP1024.12, R#13.1
Net-181: CMP585.1, CMP905.10, CMP1005.25, CMP1006.20, R.1
Net-182: CMP587.1, CMP739.1, CMP773.1, CMP783.1, CMP792.1, CMP802.1, CMP805.1, CMP1005.1, CMP1006.16, CMP1023.3
Net-183: CMP589.1, CMP591.1, CMP744.1, CMP745.1, CMP764.1, CMP904.16, CMP1005.26, CMP1006.23, CMP1024.3, R#5.1
Net-184: CMP590.1, CMP596.1, CMP747.1, CMP749.1, CMP763.1, CMP904.14, CMP1005.35, CMP1006.24, CMP1024.9, R#9.1
Net-185: CMP592.1, CMP777.1, CMP904.9, CMP905.9, CMP1005.21, CMP1006.19, CMP1022.3, D#7.2
Net-186: CMP598.1, CMP612.1, CMP742.1, CMP748.1, CMP762.1, CMP765.1, CMP904.10, CMP1005.15, CMP1006.28, CMP1024.16, R#15.1
Net-187: CMP600.1, CMP1005.2, CMP1006.2
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
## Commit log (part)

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2025-10-21 Add .gitattributes, .gitignore, README.md, and LICENSE.txt.
2025-10-21 Add Files
2025-10-21 Imagens ajustadas multicamadas
